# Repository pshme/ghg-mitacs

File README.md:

# **GHG Sensing Project**

## **Introduction and Overview**

The purpose of this research project was to find low-cost and low-power sensors and integrate them into a compact DAQ (Data Acquisition) system for use in UAVs (Unmanned Aerial Vehicles). The sensors measure GHGs (Greenhouse Gasses) in the atmosphere along with complementary ambient readings such as temperature, humidity, and pressure.

The prototype DAQ system uses the following components:

* PJRC Teensy 4.1 Arduino-based microcontroller
* Pololu 5V 2.5A Step-Down Regulator (D24V22F5)
* Pololu 3.3V Step-Up/Step-Down Regulator (S7V8F3)
* Sensirion SCD30 CO2, humidity, and temperature sensor
* Winsen MQ-4 CH4 Sensor
* Winsen MQ-9B CO and CH4 Sensor
* Winsen MQ-131 O3 Sensor
* Winsen MQ-137 NH3 Sensor
* SparkFun Barometric Pressure Sensor (MPL115A1)
* SparkFun Gas Sensor Breakout Boards
* Toggle button, LEDs, and resistors.

Each Winsen sensor was individually calibrated to determine the sensor's resistance and also convert the 5V to 3.3V output logic. The Sensirion SCD30 was calibrated by leaving the sensor powered on in an outdoor environment for 1 hour every day. The DAQ records data to the SD card every 2 seconds.

## **Basic Operation**

### **Hardware Controls**

The DAQ has 3 LEDs (one red, one green, and one blue) which represent the state of the system. There are **three** main states and **one** exception state. There is also a button which allows you to either start or end loggint to the SD card. When the DAQ is first powered on, the system is not logging any data and the red LED is *solid*. When the button is pressed, then the system can enter one of the following states: 

* *SOLID* **GREEN**, *FLASHING* **BLUE** - system is logging to SD card every 2 seconds
* *Flashing* **RED, GREEN, BLUE** - error with SD card or SD card not inserted (reboot to resolve)
* *SOLID* **RED, GREEN**, *FLASHING* **BLUE** - O3 sensor not recording data, but other sensors are (exceptions state)

To exit out of one of the four states, the button must be pressed again; however, if there is an error with the SD card or the SD card is not inserted, then you must reboot the DAQ and check that the error is resolved. 

### **Matlab Plotting**

The Arduino code (*main_ghg_code.ino*) has been modified to first display a title for each column in the .txt file. This helps simplify the Matlab import process. Once a test has been logged to the SD card, the **Import Data** function can be used. It is important to make sure that the information is *delimited* by commas and that each column is imported to Workspace as a **column vector**. After importing the section, *daq_import.m* can be ran, and the graphs will be produced. The graphs display the gas concentration, temperature, pressure, or humidity with respect to time which is converted from 2 second intervals to hours:minutes:seconds to make the graph more legible.

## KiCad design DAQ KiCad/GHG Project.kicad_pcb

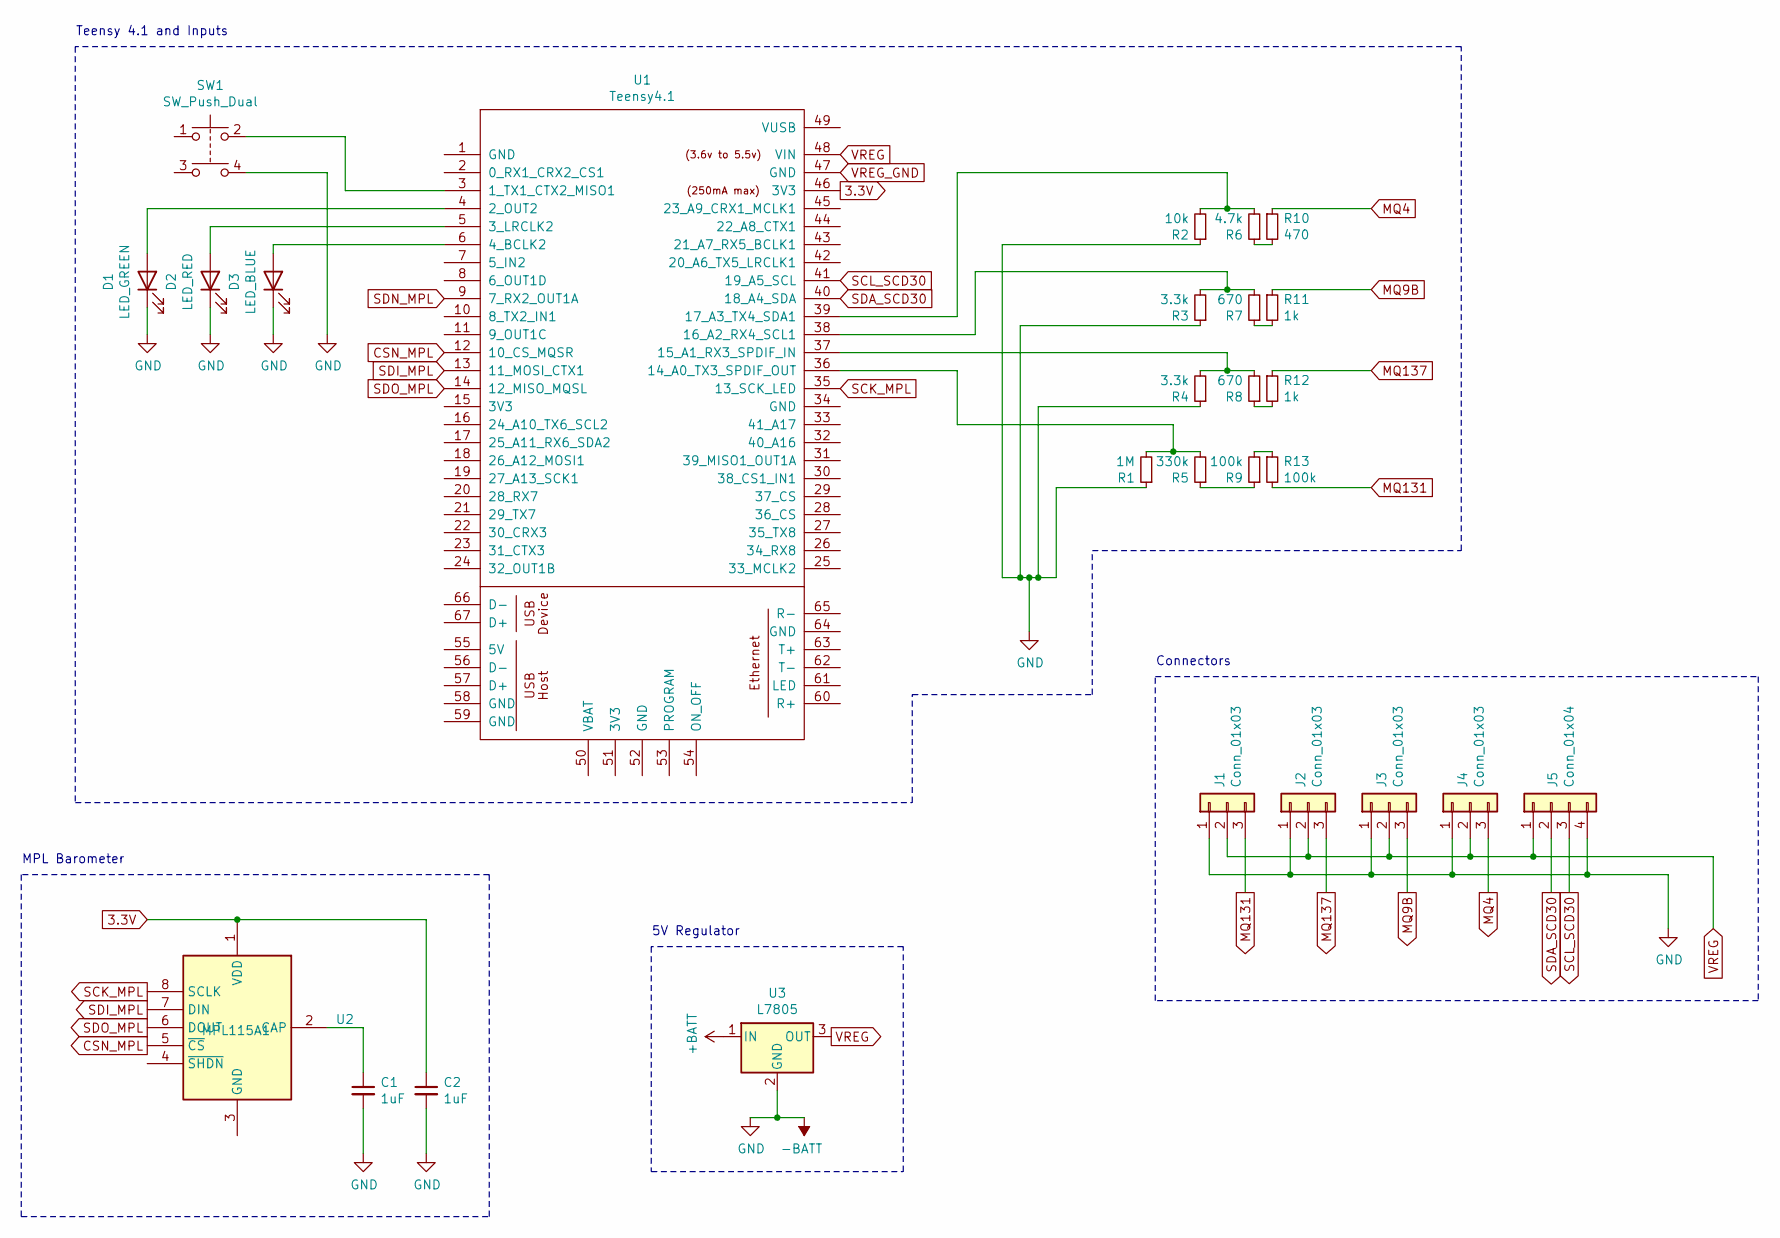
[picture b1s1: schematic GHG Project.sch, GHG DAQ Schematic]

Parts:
C1, C2: 1uF; C_0402_1005Metric
D1: LED_GREEN; LED_0603_1608Metric
D2: LED_RED; LED_0603_1608Metric
D3: LED_BLUE; LED_0603_1608Metric
J1, J2, J3, J4: Conn_01x03; JST_EH_B3B-EH-A_1x03_P2.50mm_Vertical
J5: Conn_01x04; JST_EH_B4B-EH-A_1x04_P2.50mm_Vertical
R1: 1M; R_0603_1608Metric
R2: 10k; R_0603_1608Metric
R3, R4: 3.3k; R_0603_1608Metric
R5: 330k; R_0603_1608Metric
R6: 4.7k; R_0603_1608Metric
R7, R8: 670; R_0603_1608Metric
R9, R13: 100k; R_0603_1608Metric
R10: 470; R_0603_1608Metric
R11, R12: 1k; R_0603_1608Metric
SW1: SW_Push_Dual; SW_Push_1P1T_NO_CK_KMR2
U1: Teensy4.1; Teensy41
U2: MPL115A1; NXP_LGA-8_3x5mm_P1.25mm_H1.2mm
U3: L7805

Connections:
3.3V: C2.1, U1.46 (3V3), U2.1 (VDD)
-BATT: C1.2, C2.2, D1.1 (K), D2.1 (K), D3.1 (K), J1.1, J2.1, J3.1, J4.1, J5.4, R1.1, R2.1, R3.1, R4.1, SW1.4, U3.2 (GND)
CSN_MPL: U1.12 (10_CS_MQSR), U2.5 (~CS)
MQ4: J4.3, R10.1
MQ9B: J3.3, R11.1
MQ131: J1.3, R13.2
MQ137: J2.3, R12.1
unnamed: C1.1, U2.2 (CAP)
unnamed: D1.2 (A), U1.4 (2_OUT2)
unnamed: D2.2 (A), U1.5 (3_LRCLK2)
unnamed: D3.2 (A), U1.6 (4_BCLK2)
unnamed: R1.2, R5.2, U1.36 (14_A0_TX3_SPDIF_OUT)
unnamed: R2.2, R6.2, U1.39 (17_A3_TX4_SDA1)
unnamed: R3.2, R7.2, U1.38 (16_A2_RX4_SCL1)
unnamed: R4.2, R8.2, U1.37 (15_A1_RX3_SPDIF_IN)
unnamed: R5.1, R9.1
unnamed: R6.1, R10.2
unnamed: R7.1, R11.2
unnamed: R8.1, R12.2
unnamed: R9.2, R13.1
unnamed: SW1.2, U1.3 (1_TX1_CTX2_MISO1)
SCK_MPL: U1.35 (13_SCK_LED), U2.8 (SCLK)
SCL_SCD30: J5.3, U1.41 (19_A5_SCL)
SDA_SCD30: J5.2, U1.40 (18_A4_SDA)
SDI_MPL: U1.13 (11_MOSI_CTX1), U2.7 (DIN)
SDN_MPL: U1.9 (7_RX2_OUT1A)
SDO_MPL: U1.14 (12_MISO_MQSL), U2.6 (DOUT)
VREG: J1.2, J2.2, J3.2, J4.2, J5.1, U1.48 (VIN), U3.3 (OUT)
VREG_GND: U1.47 (GND)

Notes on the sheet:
Connectors
5V Regulator
MPL Barometer
Teensy 4.1 and Inputs

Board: 2 copper layers, 26 parts (0 on the bottom side), 27 nets, no tracks yet.

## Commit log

2020-10-20 Sensor selection excel sheet
2020-10-25 MQ Arduino Code Commit
2020-11-01 main code commit
2020-11-17 Cleaned up code
2020-11-17 Added KiCad and extra Excel files
2020-12-21 Matlab code
2020-12-21 Fixed ghg_code for simpler Matlab import
2020-12-23 Fixed Matlab code
